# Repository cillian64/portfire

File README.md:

# portfire
Firework ignition control over ethernet

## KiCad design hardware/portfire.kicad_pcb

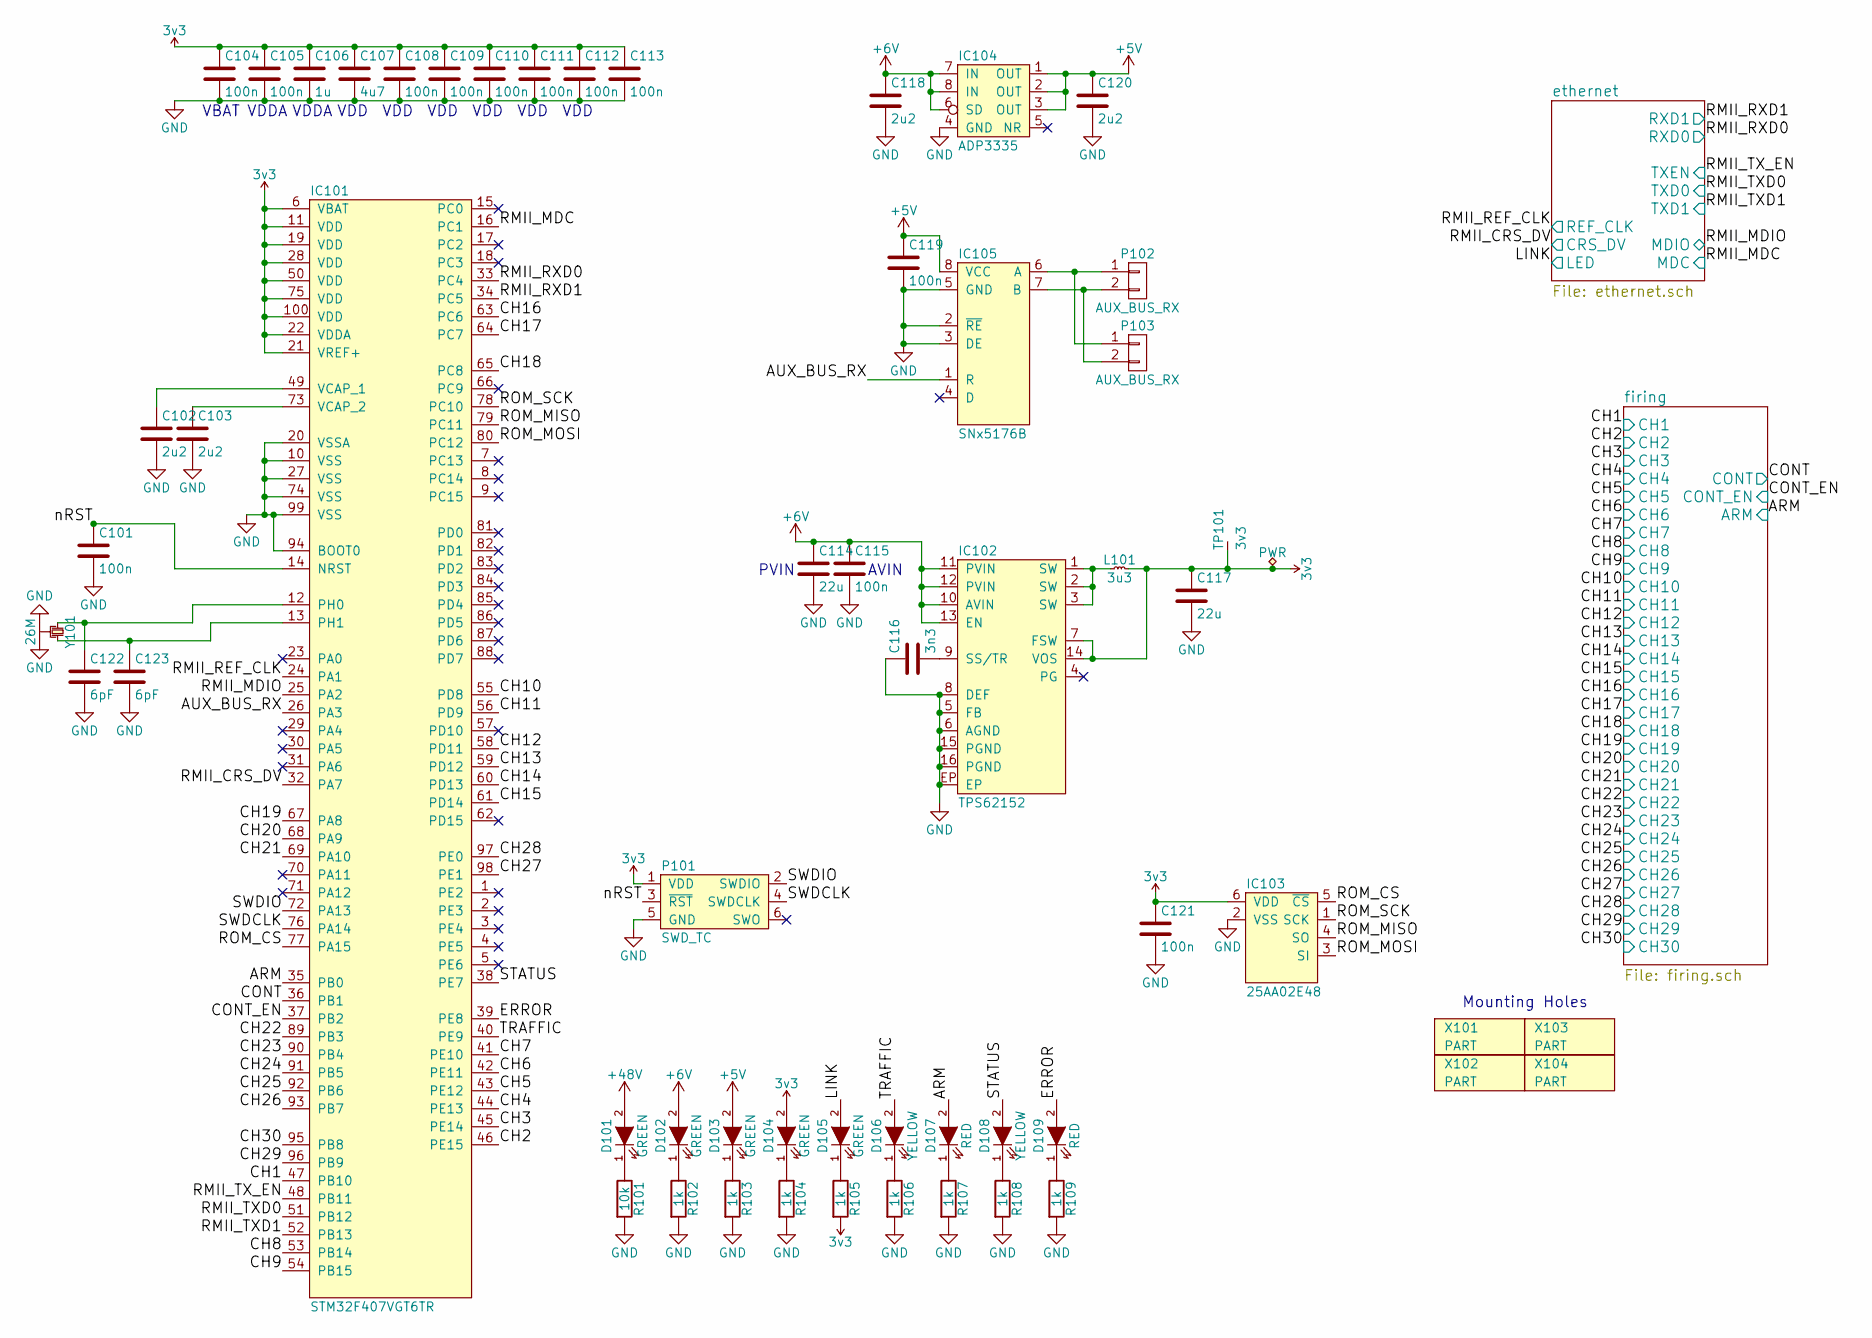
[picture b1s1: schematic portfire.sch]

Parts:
C101, C104, C105, C108, C109, C110, C111, C112, C113, C115, C119, C121: 100n; 0603; Farnell 1650835
C102, C103, C118, C120: 2u2; 0603; Farnell 2496923
C106: 1u; 0603; Farnell 9227776
C107: 4u7; 0603; Farnell 2496930
C114, C117: 22u; 1206; Farnell 1797010
C116: 3n3; 0603; Farnell 2496853
C122, C123: 6pF; 0603; Farnell 2525074
D101, D102, D103, D104, D105: GREEN; 0603-LED; Farnell 2290328
D106, D108: YELLOW; 0603-LED; Farnell 2290330
D107, D109: RED; 0603-LED; Farnell 2290329
IC101: STM32F407VGT6TR; LQFP-100; Farnell 2333297
IC102: TPS62152; QFN-16-EP-TI; Farnell 2382918
IC103: 25AA02E48; SOT-23-6; Farnell 1700995
IC104: ADP3335; MSOP-8; Farnell 2074873
IC105: SNx5176B; SOIC-8; Farnell 2395904
L101: 3u3; VLS201610HBX-1; Farnell 2455373
P101: SWD_TC; TC2030-NL
P102, P103: AUX_BUS_RX; B02B-PASK; Farnell 1830734
R101: 10k; 0603; Farnell 2303192
R102, R103, R104, R105, R106, R107, R108, R109: 1k; 0603; Farnell 9238484
TP101: 3v3; Test_point_mini
X101, X102, X103, X104: PART; M3_MOUNT
Y101: 26M; XTAL-20x16; Farnell 2455834

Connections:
3v3: C104.1, C105.1, C106.1, C107.1, C108.1, C109.1, C110.1, C111.1, C112.1, C113.1, C117.1, C121.1, D104.2 (A), IC101.6 (VBAT), IC101.11 (VDD), IC101.19 (VDD), IC101.21 (VREF+), IC101.22 (VDDA), IC101.28 (VDD), IC101.50 (VDD), IC101.75 (VDD), IC101.100 (VDD), IC102.7 (FSW), IC102.14 (VOS), IC103.6 (VDD), L101.2, P101.1 (VDD), R105.2, TP101.1; also elsewhere on the board
+5V: C119.1, C120.1, D103.2 (A), IC104.1 (OUT), IC104.2 (OUT), IC104.3 (OUT), IC105.8 (VCC)
+6V: C114.1, C115.1, C118.1, D102.2 (A), IC102.10 (AVIN), IC102.11 (PVIN), IC102.12 (PVIN), IC102.13 (EN), IC104.6 (SD), IC104.7 (IN), IC104.8 (IN); also elsewhere on the board
+48V: D101.2 (A); also elsewhere on the board
/ARM: D107.2 (A), IC101.35 (PB0); also elsewhere on the board
/AUX_BUS_RX: IC101.26 (PA3), IC105.1 (R)
/CH1: IC101.47 (PB10); also elsewhere on the board
/CH2: IC101.46 (PE15); also elsewhere on the board
/CH3: IC101.45 (PE14); also elsewhere on the board
/CH4: IC101.44 (PE13); also elsewhere on the board
/CH5: IC101.43 (PE12); also elsewhere on the board
/CH6: IC101.42 (PE11); also elsewhere on the board
/CH7: IC101.41 (PE10); also elsewhere on the board
/CH8: IC101.53 (PB14); also elsewhere on the board
/CH9: IC101.54 (PB15); also elsewhere on the board
/CH10: IC101.55 (PD8); also elsewhere on the board
/CH11: IC101.56 (PD9); also elsewhere on the board
/CH12: IC101.58 (PD11); also elsewhere on the board
/CH13: IC101.59 (PD12); also elsewhere on the board
/CH14: IC101.60 (PD13); also elsewhere on the board
/CH15: IC101.61 (PD14); also elsewhere on the board
/CH16: IC101.63 (PC6); also elsewhere on the board
/CH17: IC101.64 (PC7); also elsewhere on the board
/CH18: IC101.65 (PC8); also elsewhere on the board
/CH19: IC101.67 (PA8); also elsewhere on the board
/CH20: IC101.68 (PA9); also elsewhere on the board
/CH21: IC101.69 (PA10); also elsewhere on the board
/CH22: IC101.89 (PB3); also elsewhere on the board
/CH23: IC101.90 (PB4); also elsewhere on the board
/CH24: IC101.91 (PB5); also elsewhere on the board
/CH25: IC101.92 (PB6); also elsewhere on the board
/CH26: IC101.93 (PB7); also elsewhere on the board
/CH27: IC101.98 (PE1); also elsewhere on the board
/CH28: IC101.97 (PE0); also elsewhere on the board
/CH29: IC101.96 (PB9); also elsewhere on the board
/CH30: IC101.95 (PB8); also elsewhere on the board
/CONT: IC101.36 (PB1); also elsewhere on the board
/CONT_EN: IC101.37 (PB2); also elsewhere on the board
/ERROR: D109.2 (A), IC101.39 (PE8)
/LINK: D105.2 (A); also elsewhere on the board
/RMII_CRS_DV: IC101.32 (PA7); also elsewhere on the board
/RMII_MDC: IC101.16 (PC1); also elsewhere on the board
/RMII_MDIO: IC101.25 (PA2); also elsewhere on the board
/RMII_REF_CLK: IC101.24 (PA1); also elsewhere on the board
/RMII_RXD0: IC101.33 (PC4); also elsewhere on the board
/RMII_RXD1: IC101.34 (PC5); also elsewhere on the board
/RMII_TXD0: IC101.51 (PB12); also elsewhere on the board
/RMII_TXD1: IC101.52 (PB13); also elsewhere on the board
/RMII_TX_EN: IC101.48 (PB11); also elsewhere on the board
/ROM_CS: IC101.77 (PA15), IC103.5 (~CS)
/ROM_MISO: IC101.79 (PC11), IC103.4 (SO)
/ROM_MOSI: IC101.80 (PC12), IC103.3 (SI)
/ROM_SCK: IC101.78 (PC10), IC103.1 (SCK)
/STATUS: D108.2 (A), IC101.38 (PE7)
/SWDCLK: IC101.76 (PA14), P101.4 (SWDCLK)
/SWDIO: IC101.72 (PA13), P101.2 (SWDIO)
/TRAFFIC: D106.2 (A), IC101.40 (PE9)
/nRST: C101.1, IC101.14 (NRST), P101.3 (~RST)
GND: C101.2, C102.2, C103.2, C104.2, C105.2, C106.2, C107.2, C108.2, C109.2, C110.2, C111.2, C112.2, C113.2, C114.2, C115.2, C116.1, C117.2, C118.2, C119.2, C120.2, C121.2, C122.2, C123.2, IC101.10 (VSS), IC101.20 (VSSA), IC101.27 (VSS), IC101.74 (VSS), IC101.94 (BOOT0), IC101.99 (VSS), IC102.5 (FB), IC102.6 (AGND), IC102.8 (DEF), IC102.15 (PGND), IC102.16 (PGND), IC102.EP, IC103.2 (VSS), IC104.4 (GND), IC105.2 (~RE), IC105.3 (DE), IC105.5 (GND), P101.5 (GND), R101.2, R102.2, R103.2, R104.2, R106.2, R107.2, R108.2, R109.2, Y101.2, Y101.4; also elsewhere on the board
unnamed: C102.1, IC101.49 (VCAP_1)
unnamed: C103.1, IC101.73 (VCAP_2)
unnamed: C116.2, IC102.9 (SS/TR)
unnamed: C122.1, IC101.12 (PH0), Y101.1
unnamed: C123.1, IC101.13 (PH1), Y101.3
unnamed: D101.1 (K), R101.1
unnamed: D102.1 (K), R102.1
unnamed: D103.1 (K), R103.1
unnamed: D104.1 (K), R104.1
unnamed: D105.1 (K), R105.1
unnamed: D106.1 (K), R106.1
unnamed: D107.1 (K), R107.1
unnamed: D108.1 (K), R108.1
unnamed: D109.1 (K), R109.1
unnamed: IC102.1 (SW), IC102.2 (SW), IC102.3 (SW), L101.1
unnamed: IC105.6 (A), P102.1, P103.1
unnamed: IC105.7 (B), P102.2, P103.2

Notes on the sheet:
PVIN
AVIN
VBAT
VDDA
VDD
Mounting Holes

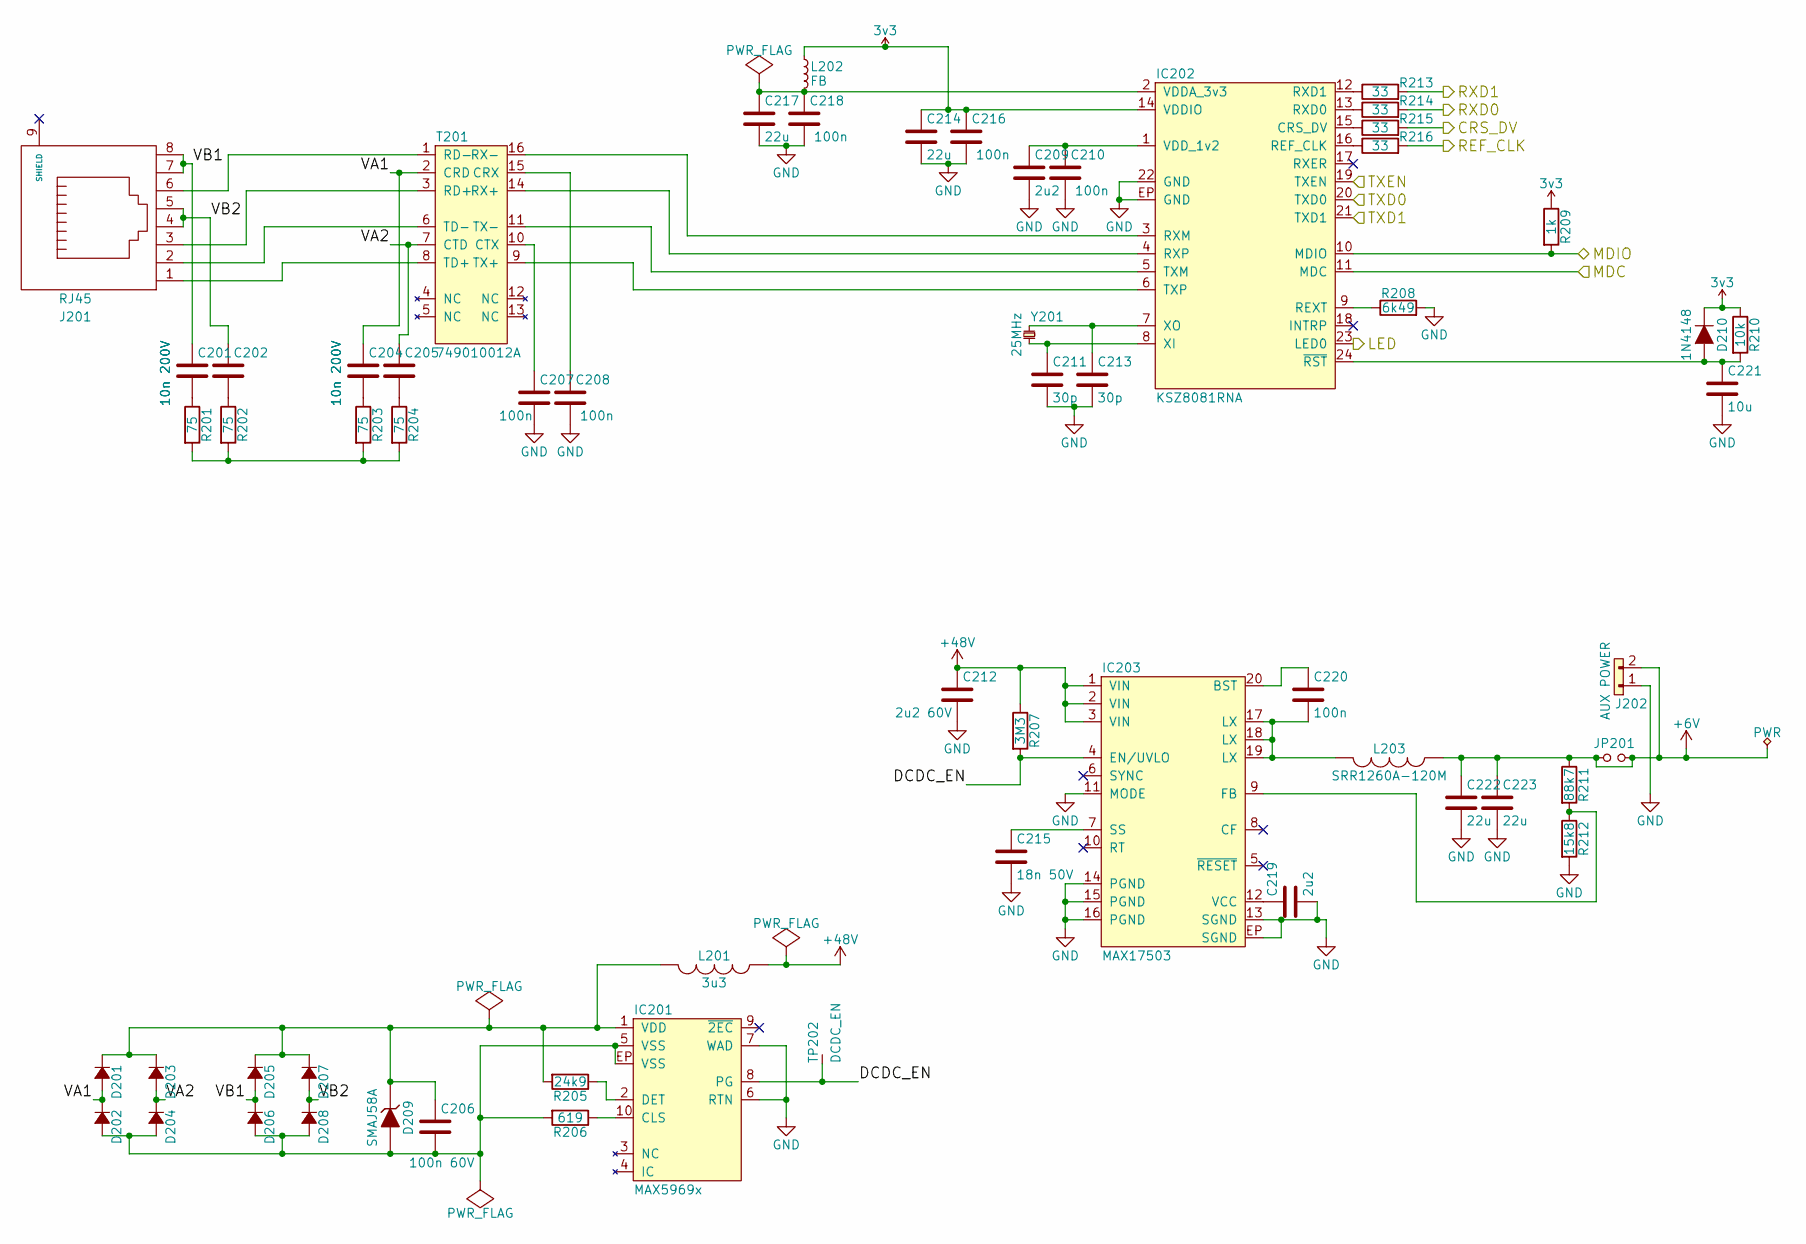
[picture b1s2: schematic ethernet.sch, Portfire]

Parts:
C201, C202, C204, C205: 10n 200V; 0805; Farnell 1828955
C206: 100n 60V; 0805; Farnell 2496941
C207, C208, C210, C216, C218, C220: 100n; 0603; Farnell 1650835
C209, C219: 2u2; 0603; Farnell 2496923
C211, C213: 30p; 0603; Farnell 2524889
C212: 2u2 60V; 1210; Farnell 1793832
C214, C217, C222, C223: 22u; 1206; Farnell 1797010
C215: 18n 50V; 0603; Farnell 1865536
C221: 10u; 0603; Farnell 2611921
D201, D202, D203, D204, D205, D206, D207, D208: SS110B; DO-214AA-SMB; Farnell 1861422
D209: SMAJ58A; DO-214AC-SMA; Farnell 1899460
D210: 1N4148; SOD-323; Farnell 1466524
IC201: MAX5969x; DFN-10-EP-MAX; Farnell 2514586
IC202: KSZ8081RNA; QFN-24-EP-MICREL; Farnell 2509802
IC203: MAX17503; QFN-20-EP-MAX; Farnell 2514229
J201: RJ45; RJHSE5380; Farnell 1860580
J202: AUX POWER; Minipow; Farnell CN13861
JP201: Jumper_NO_Small; jump
L201: 3u3; ELLATP3R3NB; Farnell 1865686
L202: FB; 0603; Farnell 1463451
L203: SRR1260A-120M; SRR1260A; Farnell 2374123
R201, R202, R203, R204: 75; 0603; Farnell 2059571
R205: 24k9; 0603; Farnell 2059450
R206: 619; 0603; Farnell 2059317
R207: 3M3; 0603; Farnell 2138666
R208: 6k49; 0603; Farnell 2059389
R209: 1k; 0603; Farnell 9238484
R210: 10k; 0603; Farnell 2303192
R211: 88k7; 0603; Farnell 2059491
R212: 15k8; 0603; Farnell 2138432
R213, R214, R215, R216: 33; 0603; Farnell 2059561
T201: 749010012A; Farnell 2422552
TP202: DCDC_EN; Test_point_mini
Y201: 25MHz; XTAL-50x32; Farnell 2101328

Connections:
3v3: C214.1, C216.1, D210.1 (K), IC202.14 (VDDIO), L202.1, R209.1, R210.1; also elsewhere on the board
+6V: C222.1, C223.1, J202.2, JP201.1, JP201.2, L203.1, R211.1; also elsewhere on the board
+48V: C212.1, IC203.1 (VIN), IC203.2 (VIN), IC203.3 (VIN), L201.1, R207.1; also elsewhere on the board
/LINK: IC202.23 (LED0); also elsewhere on the board
/RMII_CRS_DV: R215.2; also elsewhere on the board
/RMII_MDC: IC202.11 (MDC); also elsewhere on the board
/RMII_MDIO: IC202.10 (MDIO), R209.2; also elsewhere on the board
/RMII_REF_CLK: R216.2; also elsewhere on the board
/RMII_RXD0: R214.2; also elsewhere on the board
/RMII_RXD1: R213.2; also elsewhere on the board
/RMII_TXD0: IC202.20 (TXD0); also elsewhere on the board
/RMII_TXD1: IC202.21 (TXD1); also elsewhere on the board
/RMII_TX_EN: IC202.19 (TXEN); also elsewhere on the board
/ethernet/DCDC_EN: IC201.8 (PG), IC203.4 (EN/UVLO), R207.2, TP202.1
/ethernet/VA1: C204.1, D201.2 (A), D202.1 (K), T201.2 (CRD)
/ethernet/VA2: C205.1, D203.2 (A), D204.1 (K), T201.7 (CTD)
/ethernet/VB1: C201.1, D205.2 (A), D206.1 (K), J201.7, J201.8
/ethernet/VB2: C202.1, D207.2 (A), D208.1 (K), J201.4, J201.5
GND: C207.2, C208.2, C209.2, C210.2, C211.2, C212.2, C213.2, C214.2, C215.2, C216.2, C217.2, C218.2, C219.2, C221.2, C222.2, C223.2, IC201.6 (RTN), IC201.7 (WAD), IC202.22 (GND), IC202.EP (GND), IC203.11 (MODE), IC203.13 (SGND), IC203.14 (PGND), IC203.15 (PGND), IC203.16 (PGND), IC203.EP (SGND), J202.1, R208.2, R212.2; also elsewhere on the board
unnamed: C201.2, R201.1
unnamed: C202.2, R202.1
unnamed: C204.2, R203.1
unnamed: C205.2, R204.1
unnamed: C206.1, D201.1 (K), D203.1 (K), D205.1 (K), D207.1 (K), D209.1 (K), IC201.1 (VDD), L201.2, R205.2
unnamed: C206.2, D202.2 (A), D204.2 (A), D206.2 (A), D208.2 (A), D209.2 (A), IC201.5 (VSS), IC201.EP (VSS), R206.2
unnamed: C207.1, T201.10 (CTX)
unnamed: C208.1, T201.15 (CRX)
unnamed: C209.1, C210.1, IC202.1 (VDD_1v2)
unnamed: C211.1, IC202.8 (XI), Y201.2
unnamed: C213.1, IC202.7 (XO), Y201.1
unnamed: C215.1, IC203.7 (SS)
unnamed: C217.1, C218.1, IC202.2 (VDDA_3v3), L202.2
unnamed: C219.1, IC203.12 (VCC)
unnamed: C220.1, IC203.20 (BST)
unnamed: C220.2, IC203.17 (LX), IC203.18 (LX), IC203.19 (LX), L203.2
unnamed: C221.1, D210.2 (A), IC202.24 (~RST), R210.2
unnamed: IC201.2 (DET), R205.1
unnamed: IC201.10 (CLS), R206.1
unnamed: IC202.3 (RXM), T201.16 (RX-)
unnamed: IC202.4 (RXP), T201.14 (RX+)
unnamed: IC202.5 (TXM), T201.11 (TX-)
unnamed: IC202.6 (TXP), T201.9 (TX+)
unnamed: IC202.9 (REXT), R208.1
unnamed: IC202.12 (RXD1), R213.1
unnamed: IC202.13 (RXD0), R214.1
unnamed: IC202.15 (CRS_DV), R215.1
unnamed: IC202.16 (REF_CLK), R216.1
unnamed: IC203.9 (FB), R211.2, R212.1
unnamed: J201.1, T201.8 (TD+)
unnamed: J201.2, T201.6 (TD-)
unnamed: J201.3, T201.3 (RD+)
unnamed: J201.6, T201.1 (RD-)
unnamed: R201.2, R202.2, R203.2, R204.2

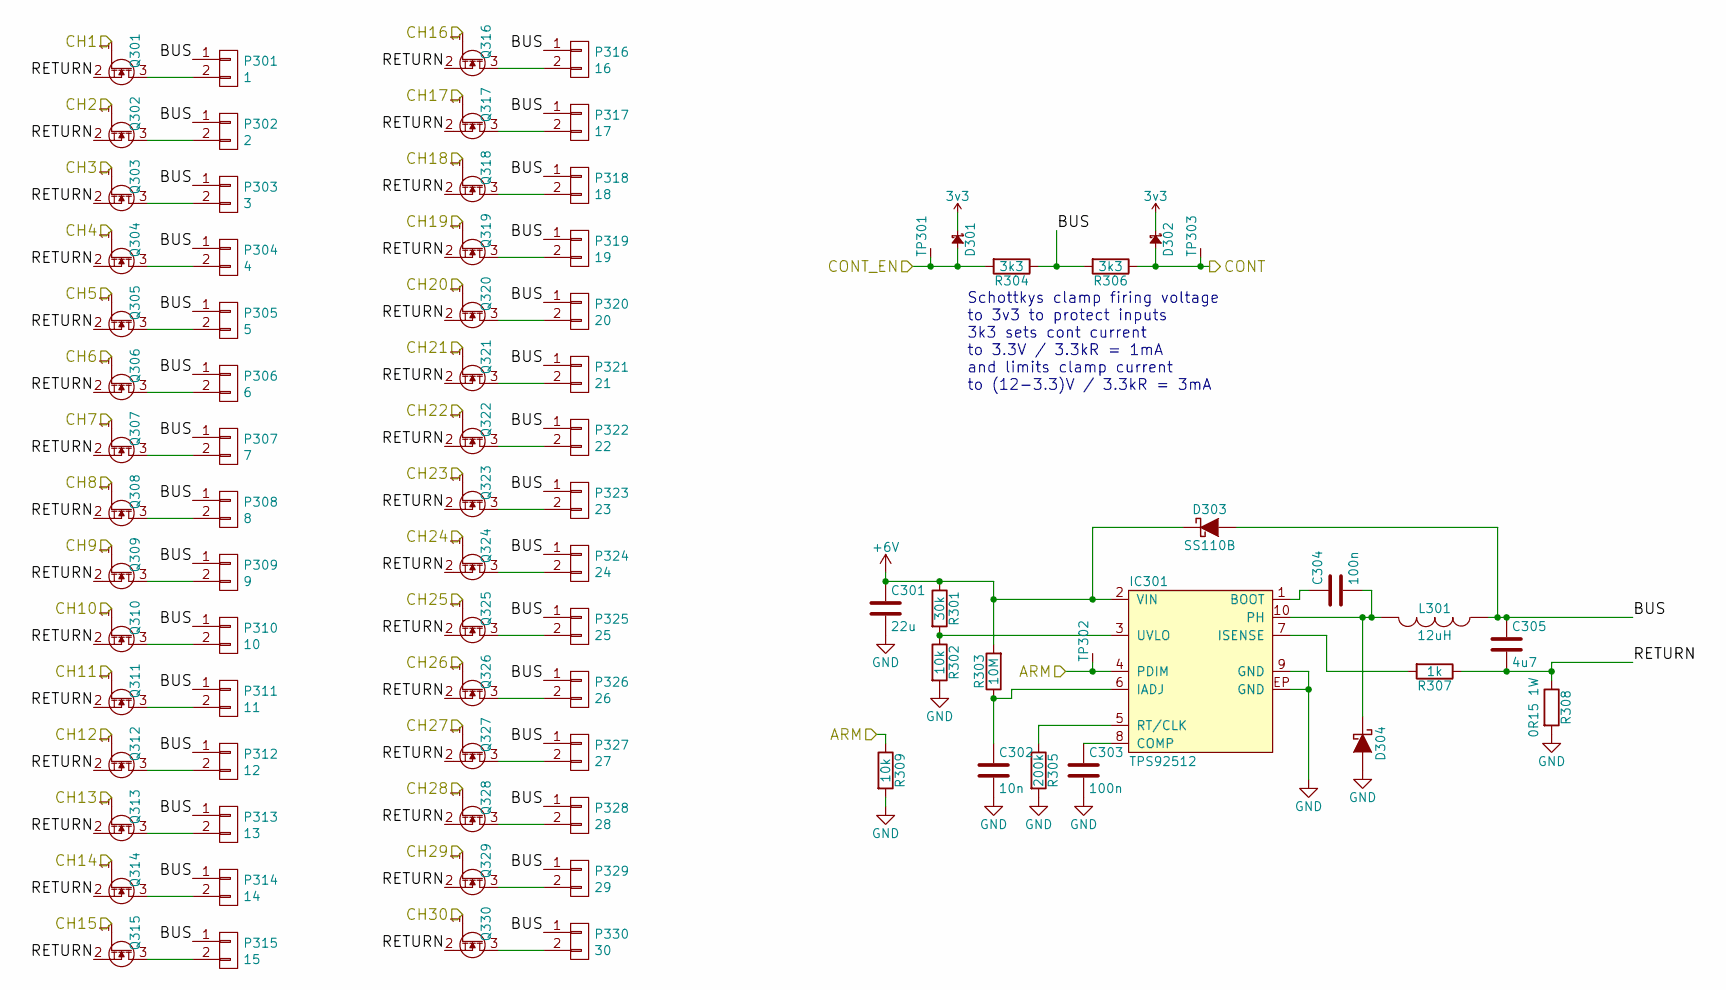
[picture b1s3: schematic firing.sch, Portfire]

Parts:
C301: 22u; 1206; Farnell 1797010
C302: 10n; 0805; Farnell 1828955
C303, C304: 100n; 0603; Farnell 1650835
C305: 4u7; 0603; Farnell 2525102
D301, D302: PMEG2005AEA; SOD-323; Farnell 8737843
D303: SS110B; DO-214AA-SMB; Farnell 1861422
D304: STPS3L40UF; DO-214AA-SMB; Farnell 2341599
IC301: TPS92512; MSOP-10-EP-TI; Farnell 2471141
L301: 12uH; SRR1260A; Farnell 2374123
P301: 1; PTSA0,52-2,5-z; Farnell 1792951
P302: 2; PTSA0,52-2,5-z; Farnell 1792951
P303: 3; PTSA0,52-2,5-z; Farnell 1792951
P304: 4; PTSA0,52-2,5-z; Farnell 1792951
P305: 5; PTSA0,52-2,5-z; Farnell 1792951
P306: 6; PTSA0,52-2,5-z; Farnell 1792951
P307: 7; PTSA0,52-2,5-z; Farnell 1792951
P308: 8; PTSA0,52-2,5-z; Farnell 1792951
P309: 9; PTSA0,52-2,5-z; Farnell 1792951
P310: 10; PTSA0,52-2,5-z; Farnell 1792951
P311: 11; PTSA0,52-2,5-z; Farnell 1792951
P312: 12; PTSA0,52-2,5-z; Farnell 1792951
P313: 13; PTSA0,52-2,5-z; Farnell 1792951
P314: 14; PTSA0,52-2,5-z; Farnell 1792951
P315: 15; PTSA0,52-2,5-z; Farnell 1792951
P316: 16; PTSA0,52-2,5-z; Farnell 1792951
P317: 17; PTSA0,52-2,5-z; Farnell 1792951
P318: 18; PTSA0,52-2,5-z; Farnell 1792951
P319: 19; PTSA0,52-2,5-z; Farnell 1792951
P320: 20; PTSA0,52-2,5-z; Farnell 1792951
P321: 21; PTSA0,52-2,5-z; Farnell 1792951
P322: 22; PTSA0,52-2,5-z; Farnell 1792951
P323: 23; PTSA0,52-2,5-z; Farnell 1792951
P324: 24; PTSA0,52-2,5-z; Farnell 1792951
P325: 25; PTSA0,52-2,5-z; Farnell 1792951
P326: 26; PTSA0,52-2,5-z; Farnell 1792951
P327: 27; PTSA0,52-2,5-z; Farnell 1792951
P328: 28; PTSA0,52-2,5-z; Farnell 1792951
P329: 29; PTSA0,52-2,5-z; Farnell 1792951
P330: 30; PTSA0,52-2,5-z; Farnell 1792951
Q301, Q302, Q303, Q304, Q305, Q306, Q307, Q308, Q309, Q310, Q311, Q312, Q313, Q314, Q315, Q316, Q317, Q318, Q319, Q320, Q321, Q322, Q323, Q324, Q325, Q326, Q327, Q328, Q329, Q330: NTR4501NT1G; SOT-23; Farnell 1431305
R301: 30k; 0603; Farnell 2059451
R302, R309: 10k; 0603; Farnell 2303192
R303: 10M; 0603; Farnell 2059699
R304, R306: 3k3; 0603; Farnell 2059614
R305: 200k; 0603; Farnell 2059509
R307: 1k; 0603; Farnell 9238484
R308: 0R15 1W; 2512; Farnell 2116453
TP301: CONT_EN; TESTPAD
TP302: ARM; TESTPAD
TP303: CONT_MEAS; TESTPAD

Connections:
3v3: D301.1, D302.1; also elsewhere on the board
+6V: C301.1, D303.1 (K), IC301.2 (VIN), R301.1, R303.2; also elsewhere on the board
/ARM: IC301.4 (PDIM), R309.1, TP302.1; also elsewhere on the board
/CH1: Q301.1 (G); also elsewhere on the board
/CH2: Q302.1 (G); also elsewhere on the board
/CH3: Q303.1 (G); also elsewhere on the board
/CH4: Q304.1 (G); also elsewhere on the board
/CH5: Q305.1 (G); also elsewhere on the board
/CH6: Q306.1 (G); also elsewhere on the board
/CH7: Q307.1 (G); also elsewhere on the board
/CH8: Q308.1 (G); also elsewhere on the board
/CH9: Q309.1 (G); also elsewhere on the board
/CH10: Q310.1 (G); also elsewhere on the board
/CH11: Q311.1 (G); also elsewhere on the board
/CH12: Q312.1 (G); also elsewhere on the board
/CH13: Q313.1 (G); also elsewhere on the board
/CH14: Q314.1 (G); also elsewhere on the board
/CH15: Q315.1 (G); also elsewhere on the board
/CH16: Q316.1 (G); also elsewhere on the board
/CH17: Q317.1 (G); also elsewhere on the board
/CH18: Q318.1 (G); also elsewhere on the board
/CH19: Q319.1 (G); also elsewhere on the board
/CH20: Q320.1 (G); also elsewhere on the board
/CH21: Q321.1 (G); also elsewhere on the board
/CH22: Q322.1 (G); also elsewhere on the board
/CH23: Q323.1 (G); also elsewhere on the board
/CH24: Q324.1 (G); also elsewhere on the board
/CH25: Q325.1 (G); also elsewhere on the board
/CH26: Q326.1 (G); also elsewhere on the board
/CH27: Q327.1 (G); also elsewhere on the board
/CH28: Q328.1 (G); also elsewhere on the board
/CH29: Q329.1 (G); also elsewhere on the board
/CH30: Q330.1 (G); also elsewhere on the board
/CONT: D302.2, R306.1, TP303.1; also elsewhere on the board
/CONT_EN: D301.2, R304.2, TP301.1; also elsewhere on the board
/firing/BUS: C305.1, D303.2 (A), L301.1, P301.1, P302.1, P303.1, P304.1, P305.1, P306.1, P307.1, P308.1, P309.1, P310.1, P311.1, P312.1, P313.1, P314.1, P315.1, P316.1, P317.1, P318.1, P319.1, P320.1, P321.1, P322.1, P323.1, P324.1, P325.1, P326.1, P327.1, P328.1, P329.1, P330.1, R304.1, R306.2
/firing/RETURN: C305.2, Q301.2 (S), Q302.2 (S), Q303.2 (S), Q304.2 (S), Q305.2 (S), Q306.2 (S), Q307.2 (S), Q308.2 (S), Q309.2 (S), Q310.2 (S), Q311.2 (S), Q312.2 (S), Q313.2 (S), Q314.2 (S), Q315.2 (S), Q316.2 (S), Q317.2 (S), Q318.2 (S), Q319.2 (S), Q320.2 (S), Q321.2 (S), Q322.2 (S), Q323.2 (S), Q324.2 (S), Q325.2 (S), Q326.2 (S), Q327.2 (S), Q328.2 (S), Q329.2 (S), Q330.2 (S), R307.1, R308.1
GND: C301.2, C302.2, C303.2, D304.2 (A), IC301.9 (GND), IC301.EP (GND), R302.2, R305.2, R308.2, R309.2; also elsewhere on the board
unnamed: C302.1, IC301.6 (IADJ), R303.1
unnamed: C303.1, IC301.8 (COMP)
unnamed: C304.1, IC301.1 (BOOT)
unnamed: C304.2, D304.1 (K), IC301.10 (PH), L301.2
unnamed: IC301.3 (UVLO), R301.2, R302.1
unnamed: IC301.5 (RT/CLK), R305.1
unnamed: IC301.7 (ISENSE), R307.2
unnamed: P301.2, Q301.3 (D)
unnamed: P302.2, Q302.3 (D)
unnamed: P303.2, Q303.3 (D)
unnamed: P304.2, Q304.3 (D)
unnamed: P305.2, Q305.3 (D)
unnamed: P306.2, Q306.3 (D)
unnamed: P307.2, Q307.3 (D)
unnamed: P308.2, Q308.3 (D)
unnamed: P309.2, Q309.3 (D)
unnamed: P310.2, Q310.3 (D)
unnamed: P311.2, Q311.3 (D)
unnamed: P312.2, Q312.3 (D)
unnamed: P313.2, Q313.3 (D)
unnamed: P314.2, Q314.3 (D)
unnamed: P315.2, Q315.3 (D)
unnamed: P316.2, Q316.3 (D)
unnamed: P317.2, Q317.3 (D)
unnamed: P318.2, Q318.3 (D)
unnamed: P319.2, Q319.3 (D)
unnamed: P320.2, Q320.3 (D)
unnamed: P321.2, Q321.3 (D)
unnamed: P322.2, Q322.3 (D)
unnamed: P323.2, Q323.3 (D)
unnamed: P324.2, Q324.3 (D)
unnamed: P325.2, Q325.3 (D)
unnamed: P326.2, Q326.3 (D)
unnamed: P327.2, Q327.3 (D)
unnamed: P328.2, Q328.3 (D)
unnamed: P329.2, Q329.3 (D)
unnamed: P330.2, Q330.3 (D)

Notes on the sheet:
Schottkys clamp firing voltage to 3v3 to protect inputs 3k3 sets cont current to 3.3V / 3.3kR = 1mA and limits clamp current to (12-3.3)V / 3.3kR = 3mA

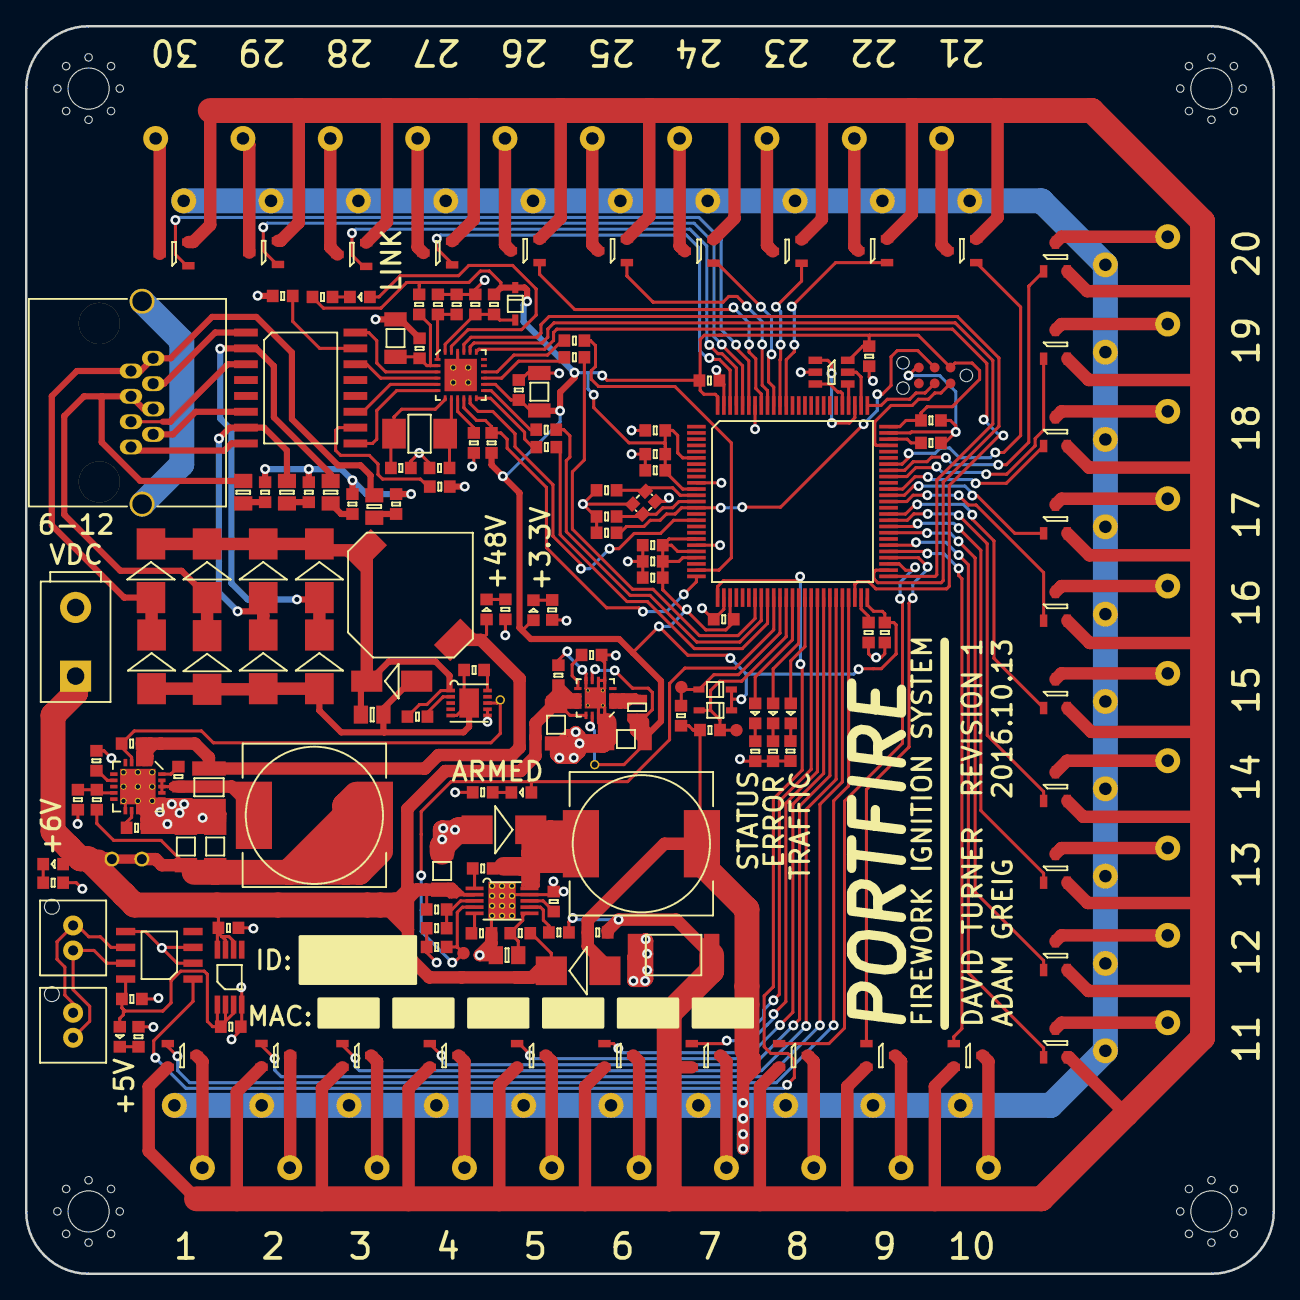
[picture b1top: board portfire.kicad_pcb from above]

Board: 2 copper layers, 100.0 x 100.0 mm, 199 parts (0 on the bottom side), 154 nets.

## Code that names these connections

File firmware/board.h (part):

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 *  GPIOA setup:
 *
 * PA0  - PIN0                         (unused).
 * PA1  - RMII_REF_CLK                 (af11).
 * PA2  - RMII_MDIO                    (af11).
 * PA3  - AUX_BUS_RX                   (af7).
 * PA4  - PIN4                         (unused).
 * PA5  - PIN5                         (unused).
 * PA6  - PIN6                         (unused).
 * PA7  - RMII_CRS_DV                  (af11).
 * PA8  - CH19                         (output, startlow).
 * PA9  - CH20                         (output, startlow).
 * PA10 - CH21                         (output, startlow).
 * PA11 - PIN11                        (unused).
 * PA12 - PIN12                        (unused).
 * PA13 - SWDIO                        (af0, pulldown).
 * PA14 - SWCLK                        (af0, pulldown).
 * PA15 - ROM_CS                       (output).
*/
#define VAL_GPIOA_MODER                (PIN_MODE_INPUT(GPIOA_PIN0) | \
                                        PIN_MODE_ALTERNATE(GPIOA_RMII_REF_CLK) | \
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/*
 *  GPIOB setup:
 *
 * PB0  - ARM                          (output, startlow).
 * PB1  - CONT                         (analog, floating).
 * PB2  - CONT_EN                      (output, startlow).
 * PB3  - CH22                         (output, startlow).
 * PB4  - CH23                         (output, startlow).
 * PB5  - CH24                         (output, startlow).
 * PB6  - CH25                         (output, startlow).
 * PB7  - CH26                         (output, startlow).
 * PB8  - CH30                         (output, startlow).
 * PB9  - CH29                         (output, startlow).
 * PB10 - CH1                          (output, startlow).
 * PB11 - RMII_TX_EN                   (af11).
 * PB12 - RMII_TXD0                    (af11).
 * PB13 - RMII_TXD1                    (af11).
 * PB14 - CH8                          (output, startlow).
 * PB15 - CH9                          (output, startlow).
*/
#define VAL_GPIOB_MODER                (PIN_MODE_OUTPUT(GPIOB_ARM) | \
                                        PIN_MODE_ANALOG(GPIOB_CONT) | \
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 *  GPIOC setup:
 *
 * PC0  - PIN0                         (unused).
 * PC1  - RMII_MDC                     (af11).
 * PC2  - PIN2                         (unused).
 * PC3  - PIN3                         (unused).
 * PC4  - RMII_RXD0                    (af11).
 * PC5  - RMII_RXD1                    (af11).
 * PC6  - CH16                         (output, startlow).
 * PC7  - CH17                         (output, startlow).
 * PC8  - CH18                         (output, startlow).
 * PC9  - PIN9                         (unused).
 * PC10 - ROM_SCK                      (af6).
 * PC11 - ROM_MISO                     (af6).
 * PC12 - ROM_MOSI                     (af6).
 * PC13 - PIN13                        (unused).
 * PC14 - PIN14                        (unused).
 * PC15 - PIN15                        (unused).
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 * PD5  - PIN5                         (unused).
 * PD6  - PIN6                         (unused).
 * PD7  - PIN7                         (unused).
 * PD8  - CH10                         (output, startlow).
 * PD9  - CH11                         (output, startlow).
 * PD10 - PIN10                        (unused).
 * PD11 - CH12                         (output, startlow).
 * PD12 - CH13                         (output, startlow).
 * PD13 - CH14                         (output, startlow).
 * PD14 - CH15                         (output, startlow).
 * PD15 - PIN15                        (unused).
*/
#define VAL_GPIOD_MODER                (PIN_MODE_INPUT(GPIOD_PIN0) | \
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/*
 *  GPIOE setup:
 *
 * PE0  - CH28                         (output, startlow).
 * PE1  - CH27                         (output, startlow).
 * PE2  - PIN2                         (unused).
 * PE3  - PIN3                         (unused).
 * PE4  - PIN4                         (unused).
 * PE5  - PIN5                         (unused).
 * PE6  - PIN6                         (unused).
 * PE7  - STATUS                       (output, startlow).
 * PE8  - ERROR                        (output, startlow).
 * PE9  - TRAFFIC                      (output, startlow).
 * PE10 - CH7                          (output, startlow).
 * PE11 - CH6                          (output, startlow).
 * PE12 - CH5                          (output, startlow).
 * PE13 - CH4                          (output, startlow).
 * PE14 - CH3                          (output, startlow).
 * PE15 - CH2                          (output, startlow).
*/
#define VAL_GPIOE_MODER                (PIN_MODE_OUTPUT(GPIOE_CH28) | \
                                        PIN_MODE_OUTPUT(GPIOE_CH27) | \
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/*
 *  GPIOH setup:
 *
 * PH0  - PIN0                         (unused).
 * PH1  - PIN1                         (unused).
 * PH2  - PIN2                         (unused).
 * PH3  - PIN3                         (unused).
 * PH4  - PIN4                         (unused).
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
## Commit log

2016-09-19 Add firing block connector footprint
2016-09-20 Added wire terminal part
2016-09-21 PoE and switcher BOM
2016-09-21 inductor footprints
2016-09-25 Added agg-kicad submodule
2016-09-26 Roughed out ethernet part of schematic
2016-09-29 Added lots of component specs around poe section
2016-10-01 SMPS schematic design
2016-10-01 Added SMPS inductor footprint
2016-10-01 Fixed fp references
2016-10-01 Hierarchical sheets, connected up RMII/PD pins
2016-10-01 Added 3v3 sync buck smps
2016-10-01 stm32 psu and SWD programming
2016-10-01 Added firing switch transistors
2016-10-02 Firing matrix and CC SMPS
2016-10-03 aux power, test points
2016-10-04 bump agg-kicad
2016-10-04 Added aux bus
2016-10-04 Fixed schematic part with derpy path
2016-10-04 LEDs, ethernet jack
2016-10-04 component grouping on pcb sheet
2016-10-04 mounting holes
2016-10-06 Added xtal to STM32
2016-10-06 Routed STM32 cruft and started on ethernet
2016-10-11 various routing
2016-10-11 Moved Bob Smith from signal gnd to chassis gnd
2016-10-11 Invert ethernet magnetics ordering.
2016-10-11 Removed pointless half of Bob Smith
2016-10-12 Lots of placement/routing
2016-10-12 Placed uc, routed RMII
2016-10-12 Routed ROM
2016-10-12 Routed cont, arm, LEDs
2016-10-12 Routed firing channels
2016-10-12 LED labels
2016-10-13 Rotate silk labels on CH21-30
2016-10-13 Shrank ethernet jack pins, beefed PD tracks
2016-10-13 Fixed ERC and DRC issues
2016-10-13 Made board beautiful
2016-10-13 add some 3d models, render
2016-10-13 update readme with image
2016-10-13 update render to white bg
2016-10-13 add sch pdf
2016-10-13 Schematic sheet annotation
2016-10-13 update cap models to capacitors
2016-10-13 crop render
2016-10-14 make pcb work with kicad 4.0.4 again
2016-10-14 update 5v ldo to correct farnell part
2016-10-14 add pulldown to ARM line
2016-10-14 remove power schematic sheet pins
2016-10-15 connect link led to 3v3 not gnd, and sign-off schematic
2016-10-15 add bom from script
2016-10-15 board tidy-up
2016-10-15 make board work in kicad 4.0.4
2016-10-15 gerbers
2016-10-15 Reduced silk linewidth slightly
2016-10-16 Removed paste from gerber zip
2016-10-17 rename edge cuts gerber
2016-10-18 first start at firmware
2016-10-19 swap to f417
2016-10-19 strip example main down to basics
2016-10-19 add ROM reading and firing control
2016-11-07 Changed LAN magnetics to PoE compat part
2016-11-09 Added BOM/stickerbom docs
2016-11-11 add continuity calibration and 3-at-once firing
2016-11-11 add instructions on patching chibios
2016-11-11 add invite stuff
2016-11-11 Fix multiple firing, fix board.h error, add bus voltage reading
2016-11-11 add net code
2016-11-11 update net_test formatting
2016-11-11 Added first attempt at case
2016-11-11 solidworks tempfile gitignore
2016-11-11 renamed case to castellated.
2016-11-11 Added new hinged case design
2016-11-12 add patchfile for lwip_ip_addr warning in latest gcc
2016-11-12 Add DHCP and autodiscovery
2016-11-15 add continuity bus voltage sensing
2016-11-16 added hinged case plots and hinge
2017-11-24 Add photo to readme.md
2018-04-09 rustblink

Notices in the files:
firmware/board.h:
ChibiOS - Copyright (C) 2006..2016 Giovanni Di Sirio
Licensed under the Apache License, Version 2.0 (the "License");
